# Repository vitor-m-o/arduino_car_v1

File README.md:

# arduino_car_v1

# DESCRIÇÃO DO PROJETO:
-  Projeto de carro de Arduino para facilitar o entendimento da programação para iniciantes.
-  Código desenvolvido para o teste de todas as funcionalidades do carro de Arduino, também para documentação das bibliotecas utilizadas para seu funcionamento, tanto como exemplos de boas maneiras e código.
-  Projeto da PCB do carro, no qual está sendo projetado para uma versão fisica aprimorada.
-  Não há versão digitalizada do antigo circuito.

# BIBLIOTECAS UTILIZADAS:
- Bibliotecas instaladas diretamente da IDE Arduino. Creditos aos seus devidos criadores.
- Ultrasonic
- U8glib
- SoftwareSerial

# NOTA:

- A conexão dos botões físicamente dos carros pode mudar por conta das condições utilizadas para variar entre os botões, porém ainda será revisado e aprimorado esta parte.

# PINAGEM:

# CARRO AMARELO:

# PINOS MOTORES:

- Ponte H N1 (MOVIMENTO ANTI-HORARIO ESQUERDA) -> 4
- Ponte H N2 (MOVIMENTO HORARIO ESQUERDA) -> 5
- Ponte H N3 (MOVIMENTO ANTI-HORARIO DIREITA) -> 11
- Ponte H N4 (MOVIMENTO HORARIO DIREITA) -> 6

# PINOS SENSORES REFLEXÃO:

- Pino sensor reflexão um -> A1
- Pino sensor reflexão dois -> A2
- Pino sensor reflexão tres -> A6
- Pino sensor reflexão quatro -> A7

# PINOS SENSORES ULTRASSONICOS:

- Pino sensor TRIG ultrassonico um -> 2
- Pino sensor ECHO ultrassonico um -> 3 
  
- Pino sensor TRIG ultrassonico dois -> 2
- Pino sensor ECHO ultrassonico dois -> 7
  
- Pino sensor TRIG ultrassonico tres -> 2
- Pino sensor ECHO ultrassonico tres -> 10

# TELA OLED:

- Pino SDA e SCL

# PINOS EXTRAS:

- Pino Divisão de tensão botões -> A0
- RX do bluetooth -> 0
- TX do bluetooth -> 1

# CARRO MARROM:

# PINOS MOTORES:

- Ponte H N1 (MOVIMENTO ANTI-HORARIO ESQUERDA) -> 4
- Ponte H N2 (MOVIMENTO HORARIO ESQUERDA) -> 5
- Ponte H N3 (MOVIMENTO ANTI-HORARIO DIREITA) -> 11
- Ponte H N4 (MOVIMENTO HORARIO DIREITA) -> 6

# PINOS SENSORES REFLEXÂO:

- Pino sensor reflexão um -> A1
- Pino sensor reflexão dois -> A2
- Pino sensor reflexão tres -> A6
- Pino sensor reflexão quatro -> A7

# PINOS SDA SCL:

- Tela OLED
- 3 Sensores Infravermelhos

# PINOS EXTRAS:

- Pino Divisão de tensão botões -> A0
- RX do bluetooth -> 0
- TX do bluetooth -> 1

# FUNÇÔES DO CÓDIGO:

- Ainda por comentar.

# Linguagem utilizada:

# Autor:

[<br><sub>Vítor Maziero Oliveira</sub>](https://github.com/vitor-m-o)

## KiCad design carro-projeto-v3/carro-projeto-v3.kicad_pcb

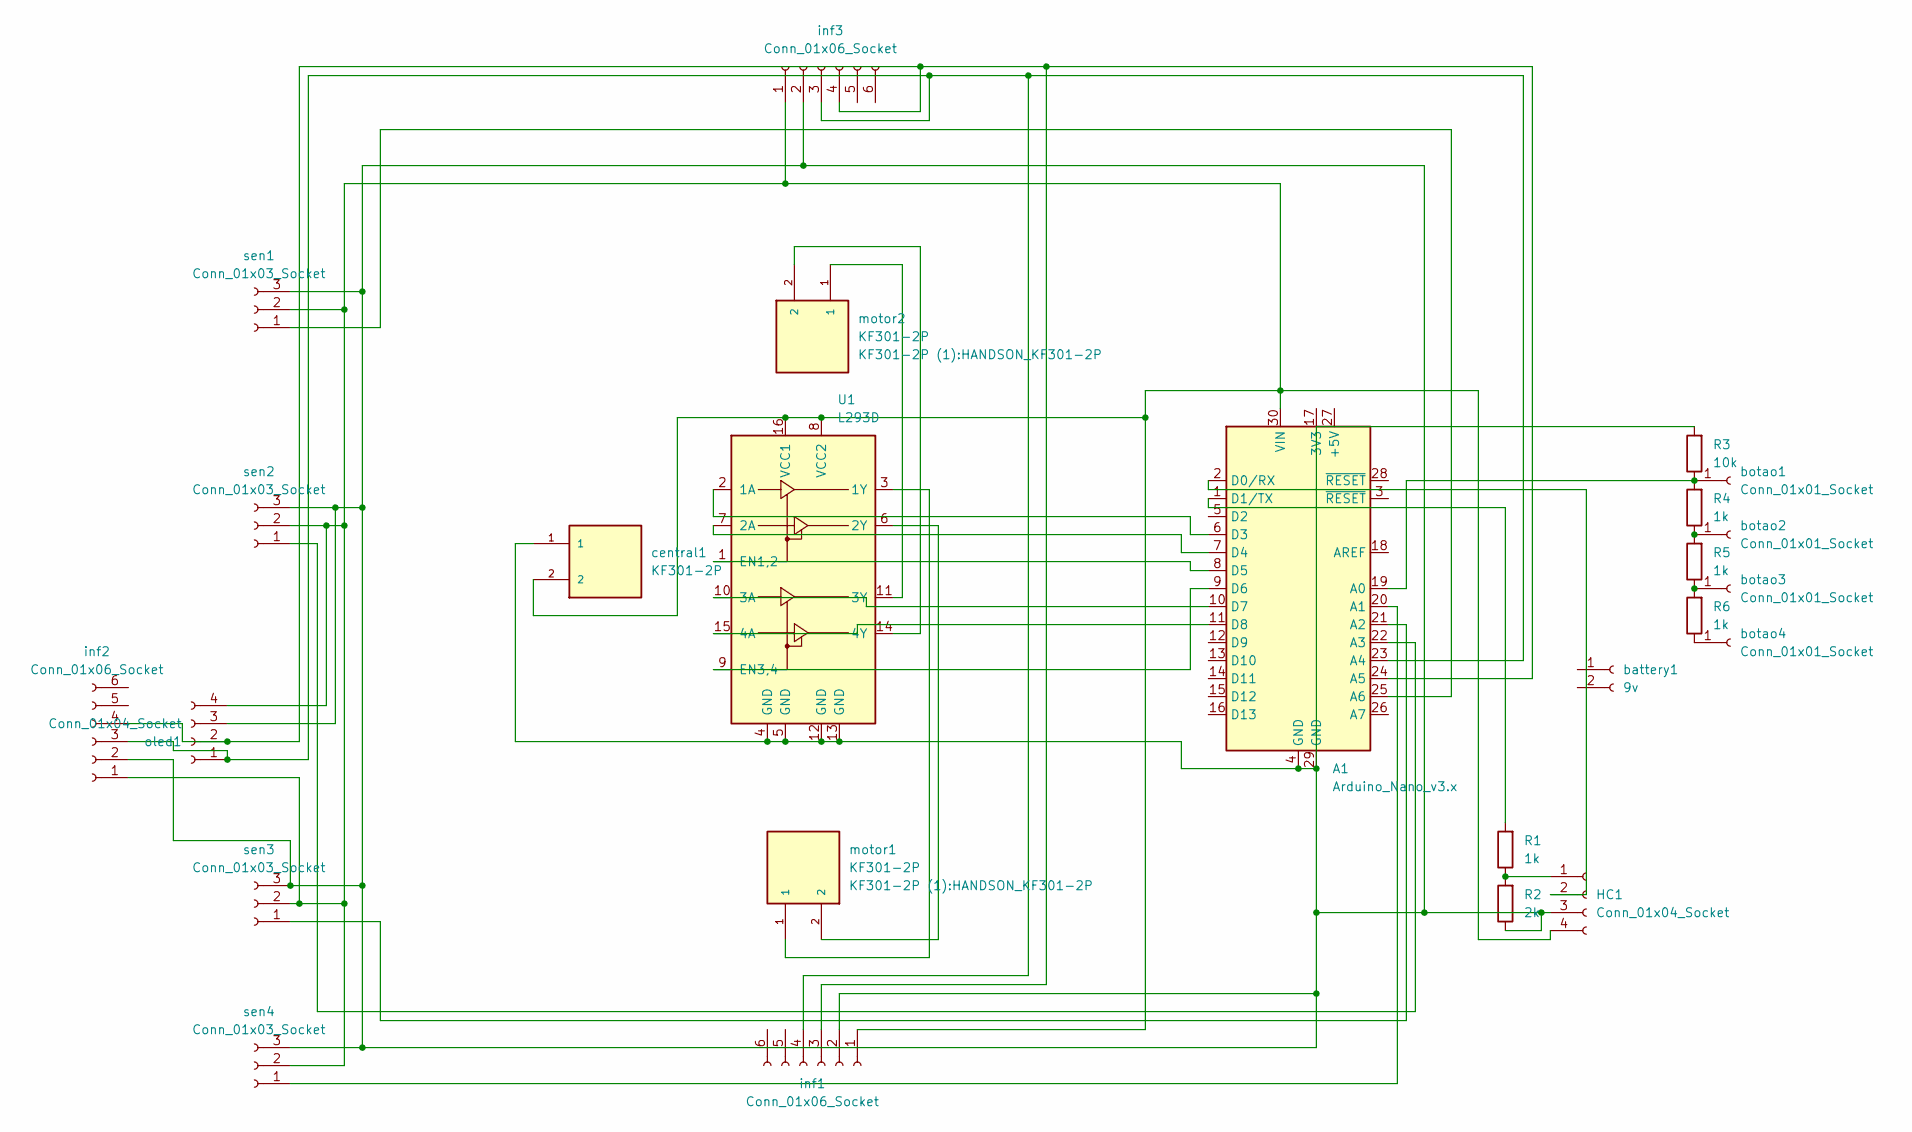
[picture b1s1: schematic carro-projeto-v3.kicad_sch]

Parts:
A1: Arduino_Nano_v3.x; Arduino_Nano
HC1: Conn_01x04_Socket; PinHeader_1x04_P2.54mm_Vertical
R1: 1k; R_Axial_DIN0204_L3.6mm_D1.6mm_P7.62mm_Horizontal
R2: 2k; R_Axial_DIN0204_L3.6mm_D1.6mm_P7.62mm_Horizontal
R3: 10k; R_Axial_DIN0207_L6.3mm_D2.5mm_P2.54mm_Vertical
R4, R5, R6: 1k; R_Axial_DIN0207_L6.3mm_D2.5mm_P2.54mm_Vertical
U1: L293D; DIP-16_W7.62mm
battery1: 9v
botao1, botao2, botao3, botao4: Conn_01x01_Socket; PinHeader_1x01_P2.54mm_Vertical
central1: KF301-2P; HANDSON_KF301-2P; PARTREV NA
inf1, inf2, inf3: Conn_01x06_Socket; PinHeader_1x06_P2.54mm_Vertical
motor1, motor2: KF301-2P; HANDSON_KF301-2P; PARTREV NA
oled1: Conn_01x04_Socket; PinHeader_1x04_P2.54mm_Vertical
sen1, sen2, sen3, sen4: Conn_01x03_Socket; PinHeader_1x03_P2.54mm_Vertical

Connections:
unnamed: A1.19 (A0), R3.1, R4.2, botao1.1
unnamed: A1.20 (A1), sen4.1
unnamed: A1.21 (A2), sen3.1
unnamed: A1.22 (A3), sen2.1
unnamed: A1.23 (A4), inf1.4, inf2.3, inf3.3, oled1.1
unnamed: A1.24 (A5), inf1.3, inf2.4, inf3.4, oled1.2
unnamed: A1.25 (A6), sen1.1
unnamed: A1.2 (D0/RX), HC1.2
unnamed: A1.1 (D1/TX), R1.2
unnamed: A1.6 (D3), U1.2 (1A)
unnamed: A1.7 (D4), U1.7 (2A)
unnamed: A1.8 (D5), U1.1 (EN1,2)
unnamed: A1.9 (D6), U1.9 (EN3,4)
unnamed: A1.10 (D7), U1.10 (3A)
unnamed: A1.11 (D8), U1.15 (4A)
unnamed: A1.30 (VIN), HC1.4, U1.8 (VCC2), U1.16 (VCC1), central1.2, inf1.1, inf2.1, inf3.1, oled1.4, sen1.2, sen2.2, sen3.2, sen4.2
unnamed: HC1.1, R1.1, R2.2
unnamed: A1.4 (GND), A1.29 (GND), HC1.3, R2.1, R3.2, U1.4 (GND), U1.5 (GND), U1.12 (GND), U1.13 (GND), central1.1, inf1.2, inf2.2, inf3.2, oled1.3, sen1.3, sen2.3, sen3.3, sen4.3
unnamed: U1.3 (1Y), motor1.1
unnamed: U1.6 (2Y), motor1.2
unnamed: U1.11 (3Y), motor2.1
unnamed: U1.14 (4Y), motor2.2
unnamed: R4.1, R5.2, botao2.1
unnamed: R5.1, R6.2, botao3.1
unnamed: R6.1, botao4.1

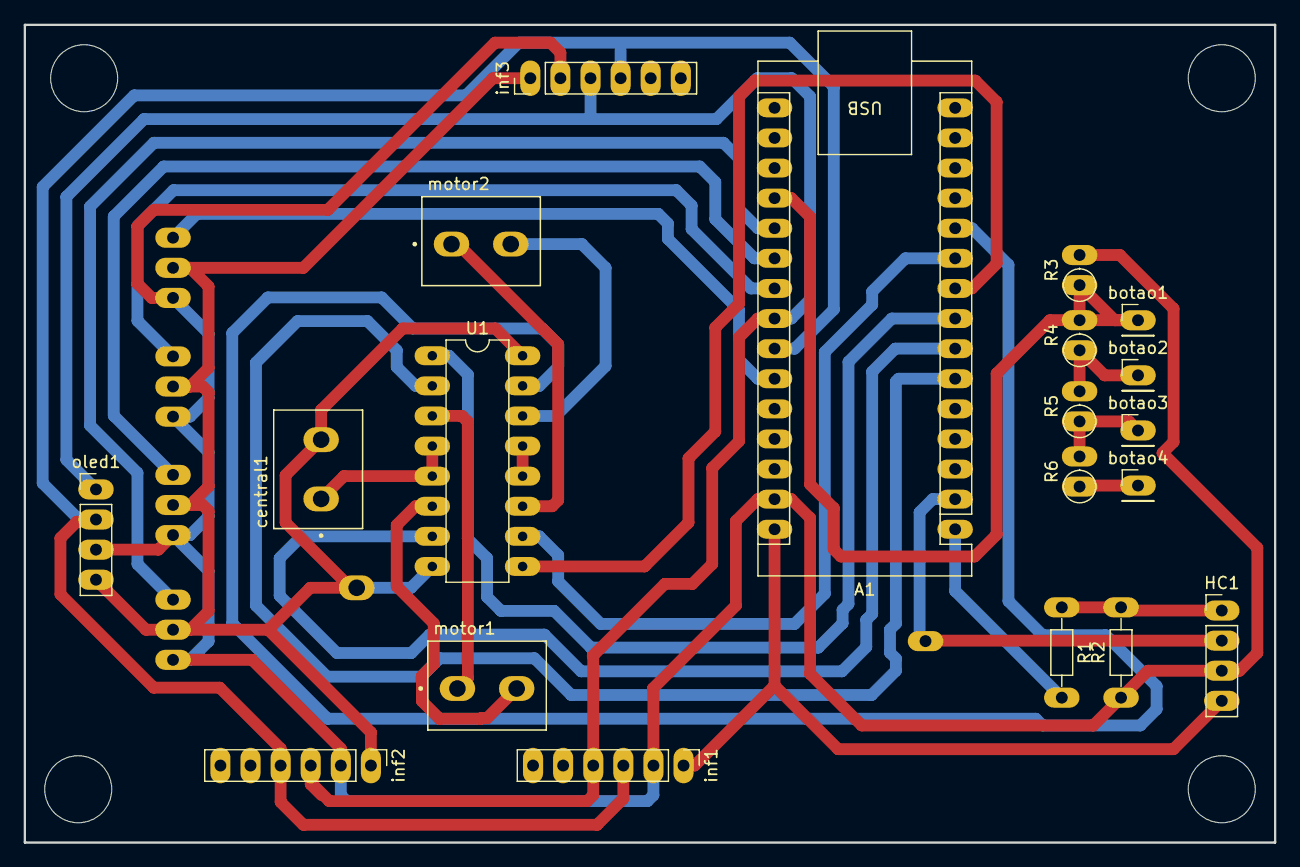
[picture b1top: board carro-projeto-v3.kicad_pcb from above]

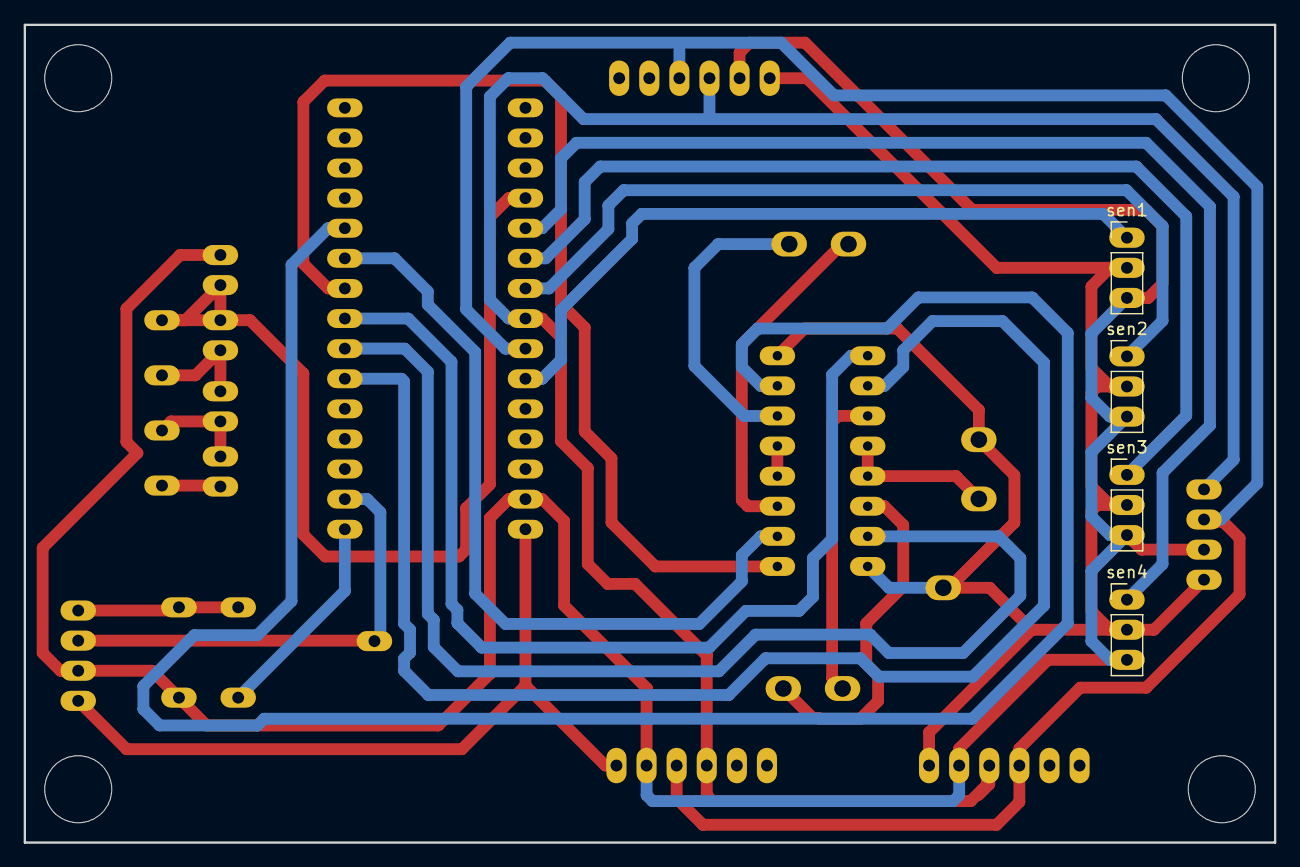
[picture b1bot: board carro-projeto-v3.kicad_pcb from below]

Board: 2 copper layers, 105.5 x 69.0 mm, 24 parts (4 on the bottom side), 25 nets.

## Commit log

2025-03-03 Rename ARDUINO-PROJECT-3.ino to ARDUINO-CAR-V1.ino
2025-03-03 KiCad PCB project for a new physical version
2025-03-03 Definir linguagem como Arduino
2025-03-19 update kicad project
